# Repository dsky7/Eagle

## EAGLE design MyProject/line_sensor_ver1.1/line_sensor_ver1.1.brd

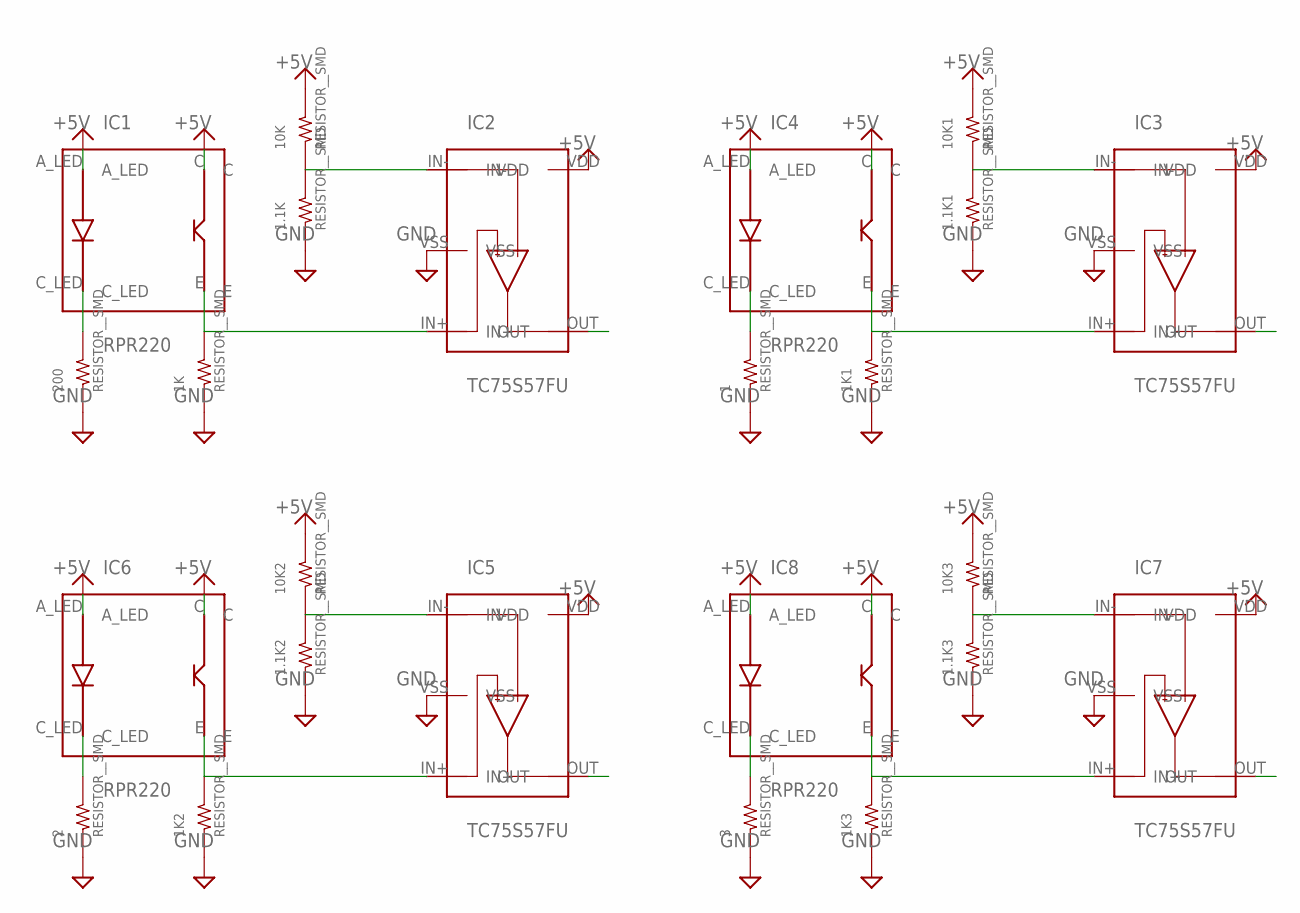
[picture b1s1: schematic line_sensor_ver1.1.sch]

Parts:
1, 1.1K, 1.1K1, 1.1K2, 1.1K3, 1K, 1K1, 1K2, 1K3, 2, 3, 10K, 10K1, 10K2, 10K3, 200: RESISTOR__SMD; 1608
IC1, IC4, IC6, IC8: RPR220
IC2, IC3, IC5, IC7: TC75S57FU; SSOP5-P-0.65A

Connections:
+5V: 10K.2, 10K1.2, 10K2.2, 10K3.2, IC1.A_LED, IC1.C, IC2.VDD, IC3.VDD, IC4.A_LED, IC4.C, IC5.VDD, IC6.A_LED, IC6.C, IC7.VDD, IC8.A_LED, IC8.C
GND: 1.1, 1.1K.1, 1.1K1.1, 1.1K2.1, 1.1K3.1, 1K.1, 1K1.1, 1K2.1, 1K3.1, 2.1, 3.1, 200.1, IC2.VSS, IC3.VSS, IC5.VSS, IC7.VSS
unnamed: 1.1K.2, 10K.1, IC2.IN-
unnamed: 1K.2, IC1.E, IC2.IN+
unnamed: 200.2, IC1.C_LED
unnamed: 1.1K1.2, 10K1.1, IC3.IN-
unnamed: 1K1.2, IC3.IN+, IC4.E
unnamed: 1.2, IC4.C_LED
unnamed: 1.1K3.2, 10K3.1, IC7.IN-
unnamed: 1.1K2.2, 10K2.1, IC5.IN-
unnamed: 1K3.2, IC7.IN+, IC8.E
unnamed: 1K2.2, IC5.IN+, IC6.E
unnamed: 2.2, IC6.C_LED
unnamed: 3.2, IC8.C_LED
OUT1: IC2.OUT
OUT2: IC3.OUT
OUT3: IC5.OUT
OUT4: IC7.OUT

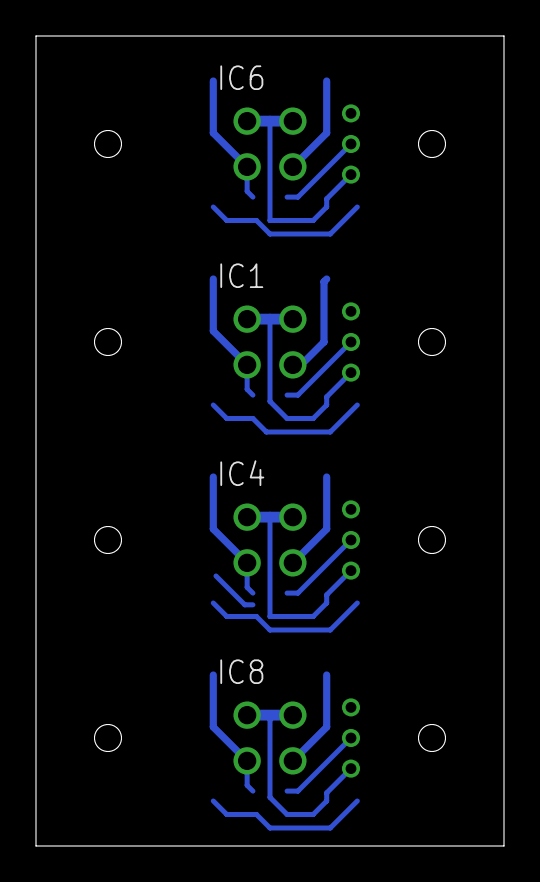
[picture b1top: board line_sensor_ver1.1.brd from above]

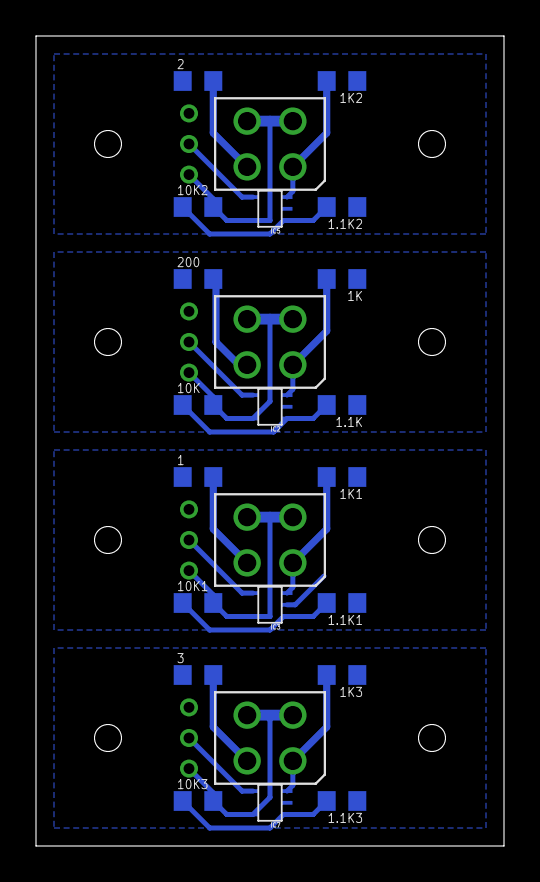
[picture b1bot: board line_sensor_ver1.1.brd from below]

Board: 2 copper layers, 26.0 x 45.0 mm, 24 parts (20 on the bottom side), 14 nets.

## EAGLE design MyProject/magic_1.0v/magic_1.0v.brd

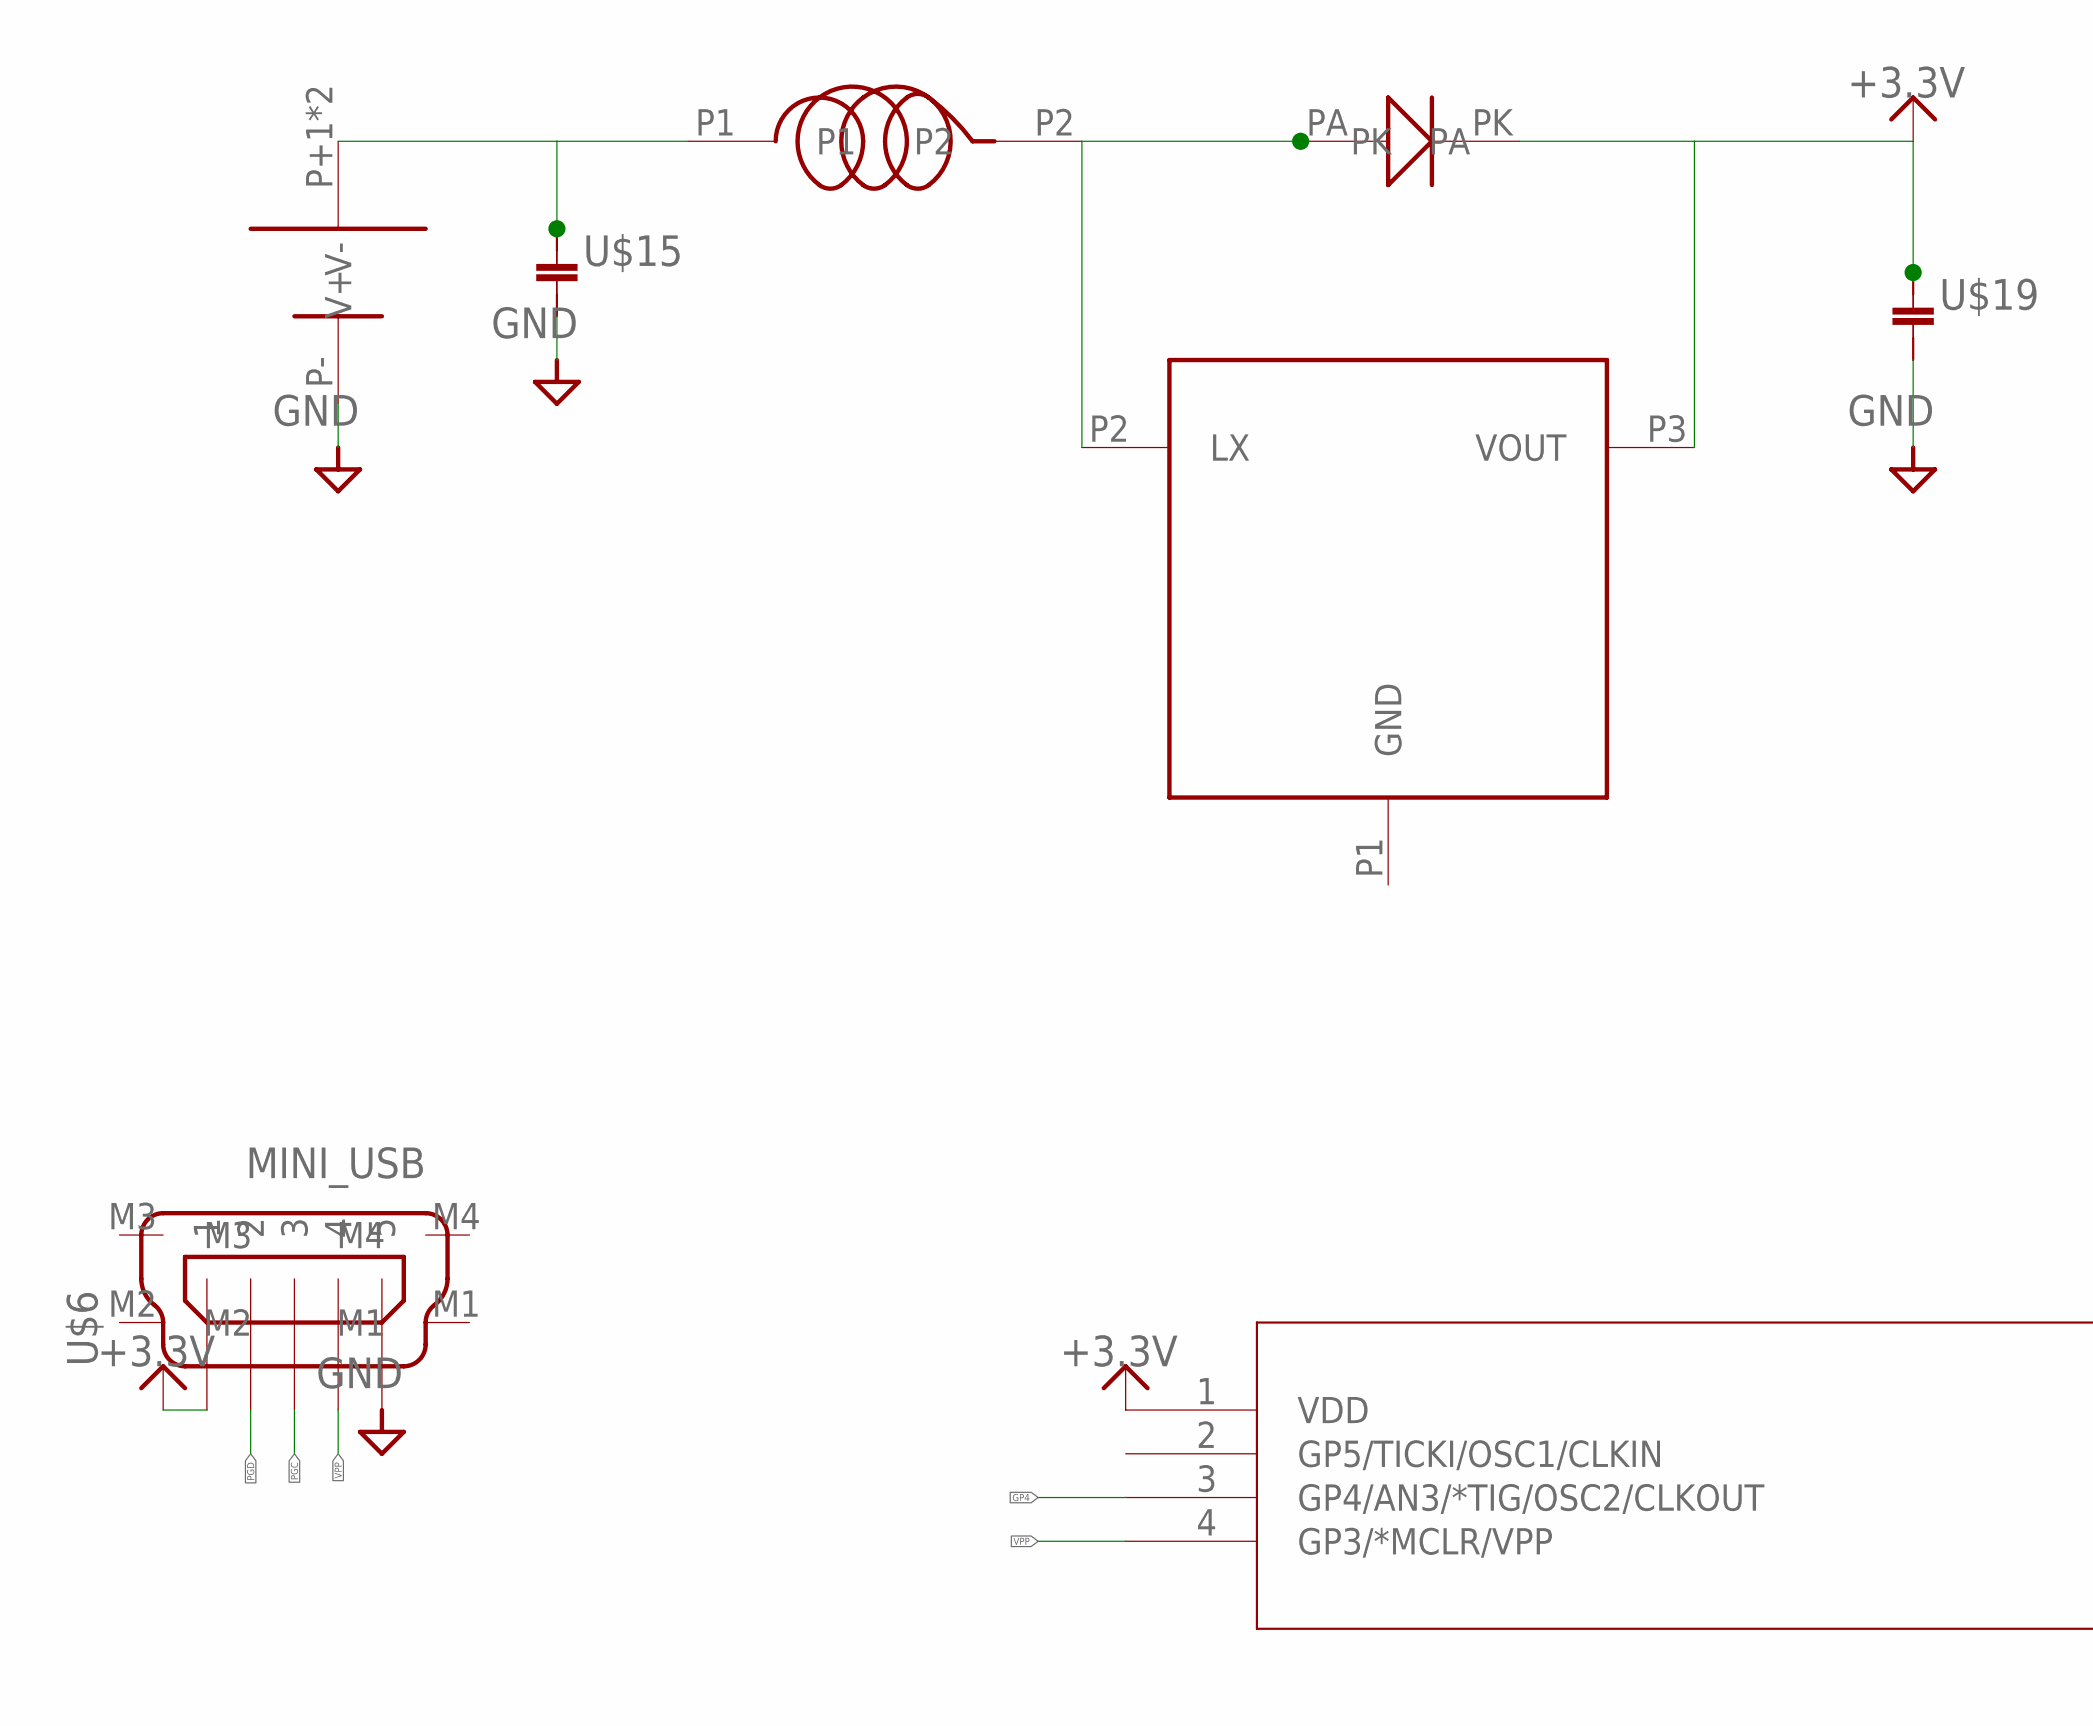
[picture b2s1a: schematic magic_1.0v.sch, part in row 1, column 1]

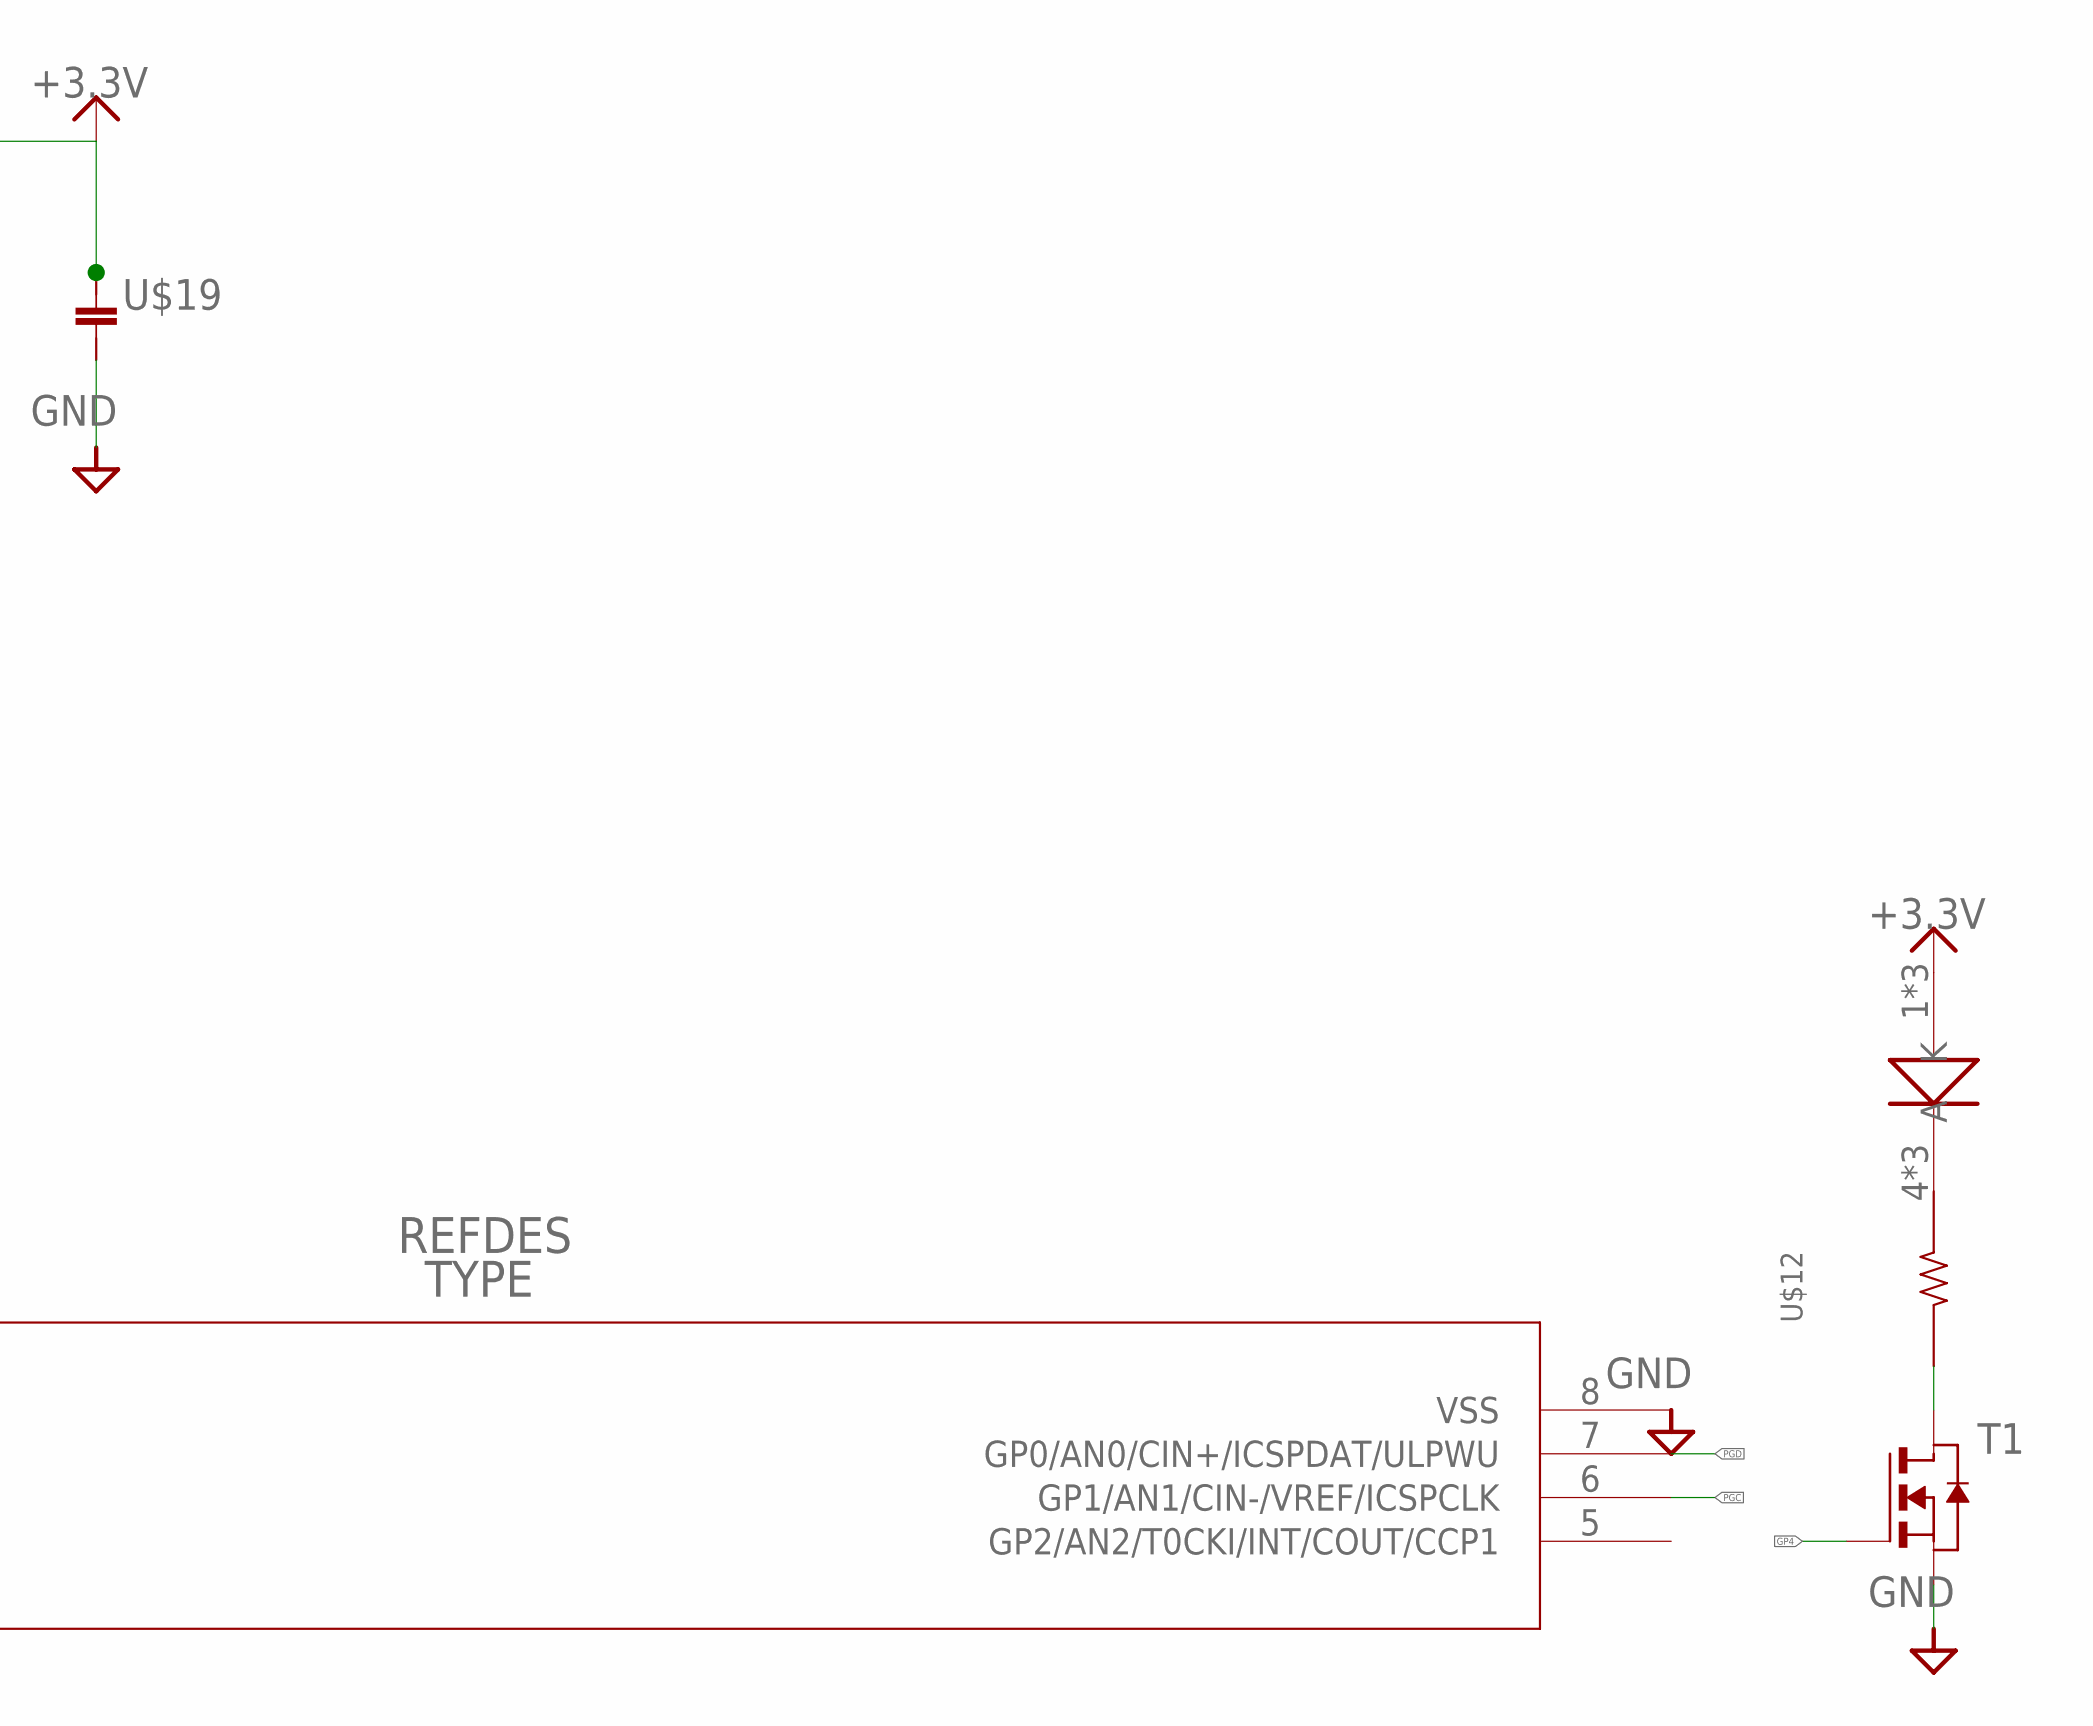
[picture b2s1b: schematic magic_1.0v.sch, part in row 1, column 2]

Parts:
T1: NMOSSOT23; SOT-23
U$1: PIC12F683-X/SN; SOIC8-N_MC
U$2: CR2032; SMTM2032
U$6: MINI_USB
U$9: OSB64; ＯＳＢ６４
U$12: RESISTOR__SMD; 1608
U$13: NPI16W
U$14: HT7733; SOT23
U$15: 3225
U$17: RSX101; TUMD2
U$19: 2012

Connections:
+3.3V: U$1.1 (VDD), U$6.1, U$9.1 (A), U$9.2 (A), U$9.3 (A), U$14.P3 (VOUT), U$17.PK, U$19.1
GND: T1.2 (S), U$1.8 (VSS), U$2.P- (V-), U$6.5, U$15.P$2 (2), U$19.2
GP4: T1.3 (G), U$1.3 (GP4/AN3/*TIG/OSC2/CLKOUT)
unnamed: U$9.4 (K), U$9.5 (K), U$9.6 (K), U$12.2
unnamed: T1.1 (D), U$12.1
unnamed: U$2.P+1 (V+), U$2.P+2 (V+), U$13.P1, U$15.P$1 (1)
unnamed: U$13.P2, U$14.P2 (LX), U$17.PA
PGC: U$1.6 (GP1/AN1/CIN-/VREF/ICSPCLK), U$6.3
PGD: U$1.7 (GP0/AN0/CIN+/ICSPDAT/ULPWU), U$6.2
VPP: U$1.4 (GP3/*MCLR/VPP), U$6.4

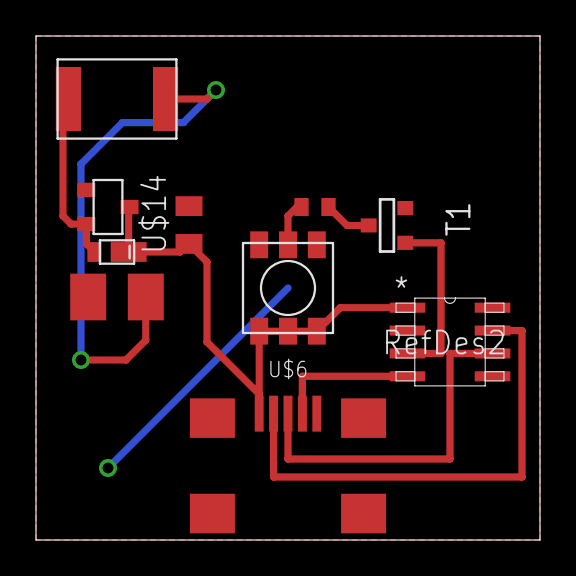
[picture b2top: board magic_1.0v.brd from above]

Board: 2 copper layers, 28.0 x 28.0 mm, 11 parts (1 on the bottom side), 10 nets.

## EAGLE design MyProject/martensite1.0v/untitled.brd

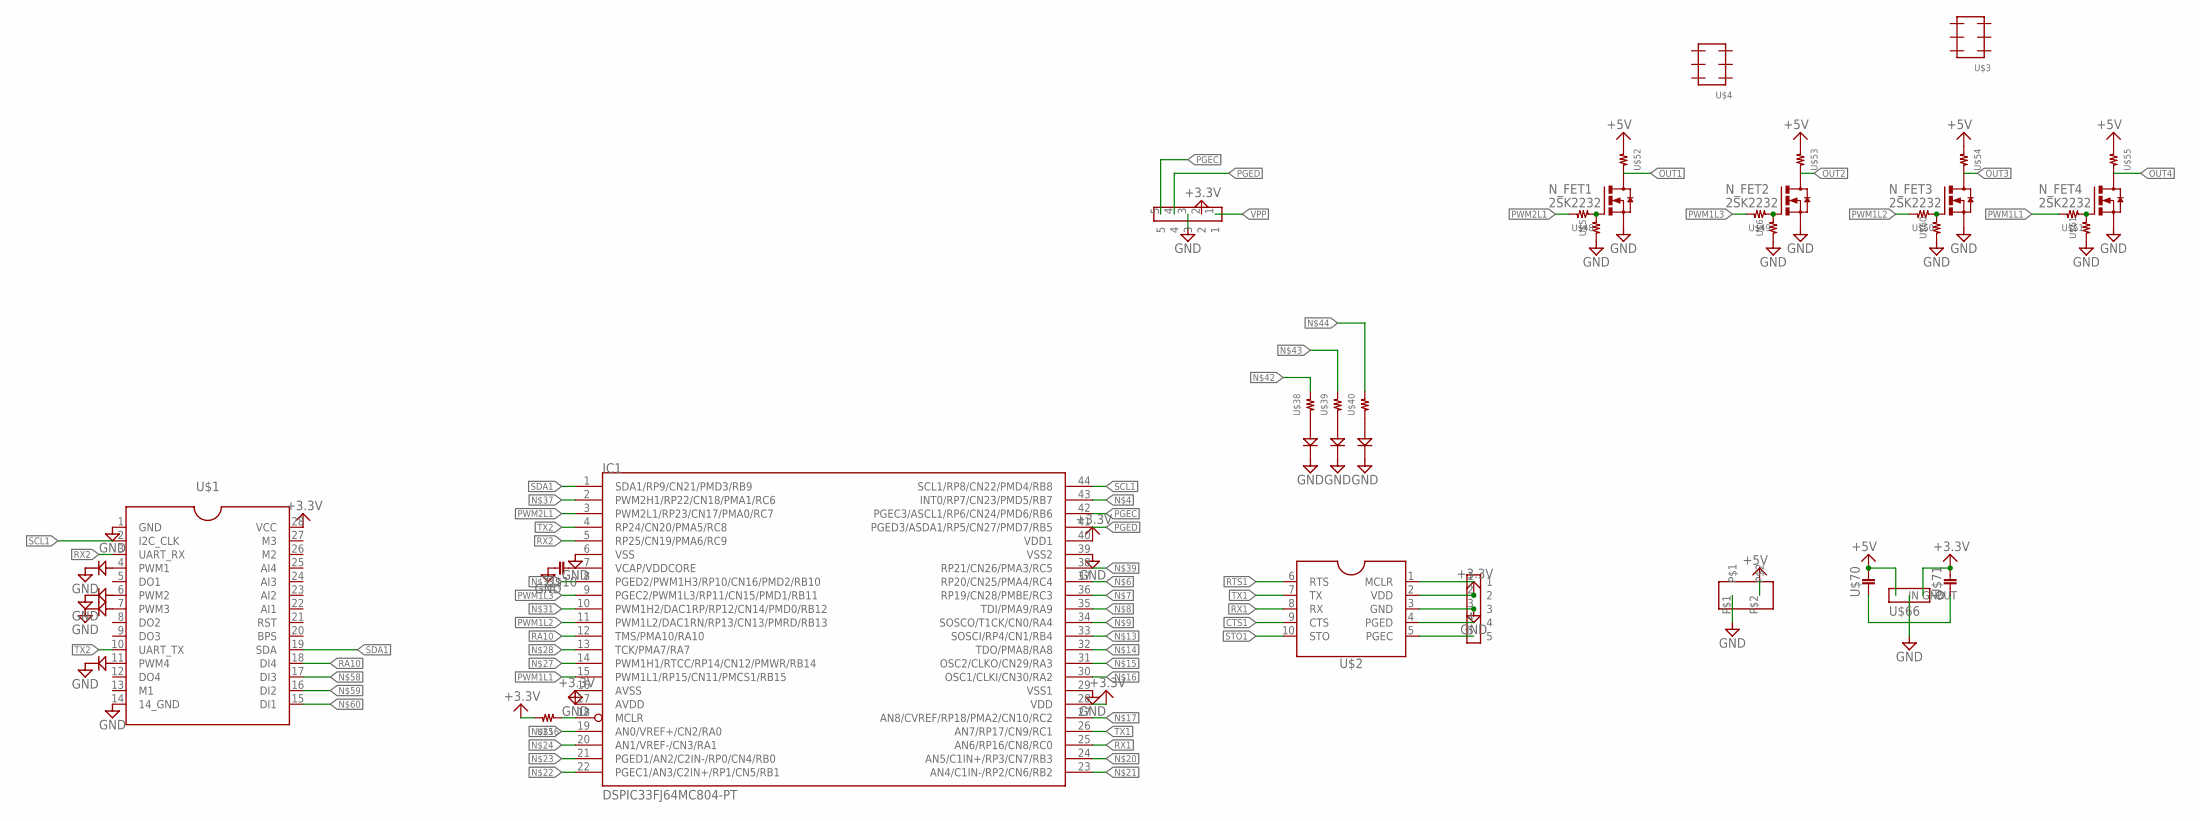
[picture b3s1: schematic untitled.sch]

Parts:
IC1: DSPIC33FJ64MC804-PT; TQFP44
N_FET1, N_FET2, N_FET3, N_FET4: 2SK2232; TO-220_V
U$1: TWE-LITE; DIP28
U$2: SBDBT; DIL10
U$3, U$4: PIN_HEADER_32; PIN_HEADER_3*2
U$5, U$6, U$16, U$38, U$39, U$40, U$48, U$49, U$50, U$51, U$52, U$53, U$54, U$55, U$60, U$61: RESISTOR__SMD; 1608
U$10: 2012
U$18, U$24: PIN_HEADER_5
U$27, U$28, U$29, U$30: 5MMLED; 5MM
U$35, U$36, U$37: 3MMLED; 3MM
U$66: TA48M033F; ＴＡ４８
U$70: 1608
U$71: 3225
U$72: PIN_HEADER_2; PIN_HEADER_2S

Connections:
+3.3V: IC1.17 (AVDD), IC1.28 (VDD), IC1.40 (VDD1), U$1.28 (VCC), U$2.2 (VDD), U$16.2, U$18.2, U$24.2, U$66.3 (OUT), U$71.P$1 (1)
+5V: U$52.1, U$53.1, U$54.1, U$55.1, U$66.1 (IN), U$70.P$1 (1), U$72.P$2
CTS1: U$2.9 (CTS)
GND: IC1.6 (VSS), IC1.16 (AVSS), IC1.29 (VSS1), IC1.39 (VSS2), N_FET1.3 (S), N_FET2.3 (S), N_FET3.3 (S), N_FET4.3 (S), U$1.1 (GND), U$1.14 (14_GND), U$2.3 (GND), U$5.1, U$6.1, U$10.1, U$18.3, U$24.3, U$27.K, U$28.K, U$29.K, U$30.K, U$35.K, U$36.K, U$37.K, U$60.1, U$61.1, U$66.2 (GND), U$70.P$2 (2), U$71.P$2 (2), U$72.P$1
unnamed: U$35.A, U$38.1
unnamed: U$2.4 (PGED), U$24.4
unnamed: U$2.1 (MCLR), U$24.1
unnamed: U$2.5 (PGEC), U$24.5
unnamed: U$1.4 (PWM1), U$27.A
unnamed: U$1.6 (PWM2), U$28.A
unnamed: U$1.7 (PWM3), U$29.A
unnamed: U$1.11 (PWM4), U$30.A
unnamed: U$36.A, U$39.1
unnamed: U$37.A, U$40.1
unnamed: N_FET1.1 (G), U$5.2, U$48.1
unnamed: N_FET2.1 (G), U$6.2, U$49.1
unnamed: N_FET3.1 (G), U$50.1, U$60.2
unnamed: N_FET4.1 (G), U$51.1, U$61.2
OUT1: N_FET1.2 (D), U$52.2
OUT2: N_FET2.2 (D), U$53.2
OUT3: N_FET3.2 (D), U$54.2
OUT4: N_FET4.2 (D), U$55.2
PGEC: IC1.42 (PGEC3/ASCL1/RP6/CN24/PMD6/RB6), U$18.5
PGED: IC1.41 (PGED3/ASDA1/RP5/CN27/PMD7/RB5), U$18.4
PWM1L1: IC1.15 (PWM1L1/RP15/CN11/PMCS1/RB15), U$51.2
PWM1L2: IC1.11 (PWM1L2/DAC1RN/RP13/CN13/PMRD/RB13), U$50.2
PWM1L3: IC1.9 (PGEC2/PWM1L3/RP11/CN15/PMD1/RB11), U$49.2
PWM2L1: IC1.3 (PWM2L1/RP23/CN17/PMA0/RC7), U$48.2
RA10: IC1.12 (TMS/PMA10/RA10), U$1.18 (DI4)
RTS1: U$2.6 (RTS)
RX1: IC1.25 (AN6/RP16/CN8/RC0), U$2.8 (RX)
RX2: IC1.5 (RP25/CN19/PMA6/RC9), U$1.3 (UART_RX)
SCL1: IC1.44 (SCL1/RP8/CN22/PMD4/RB8), U$1.2 (I2C_CLK)
SDA1: IC1.1 (SDA1/RP9/CN21/PMD3/RB9), U$1.19 (SDA)
STO1: U$2.10 (STO)
TX1: IC1.26 (AN7/RP17/CN9/RC1), U$2.7 (TX)
TX2: IC1.4 (RP24/CN20/PMA5/RC8), U$1.10 (UART_TX)
VCAP/VDDCORE: IC1.7 (VCAP/VDDCORE), U$10.2
VPP: IC1.18 (MCLR), U$16.1, U$18.1

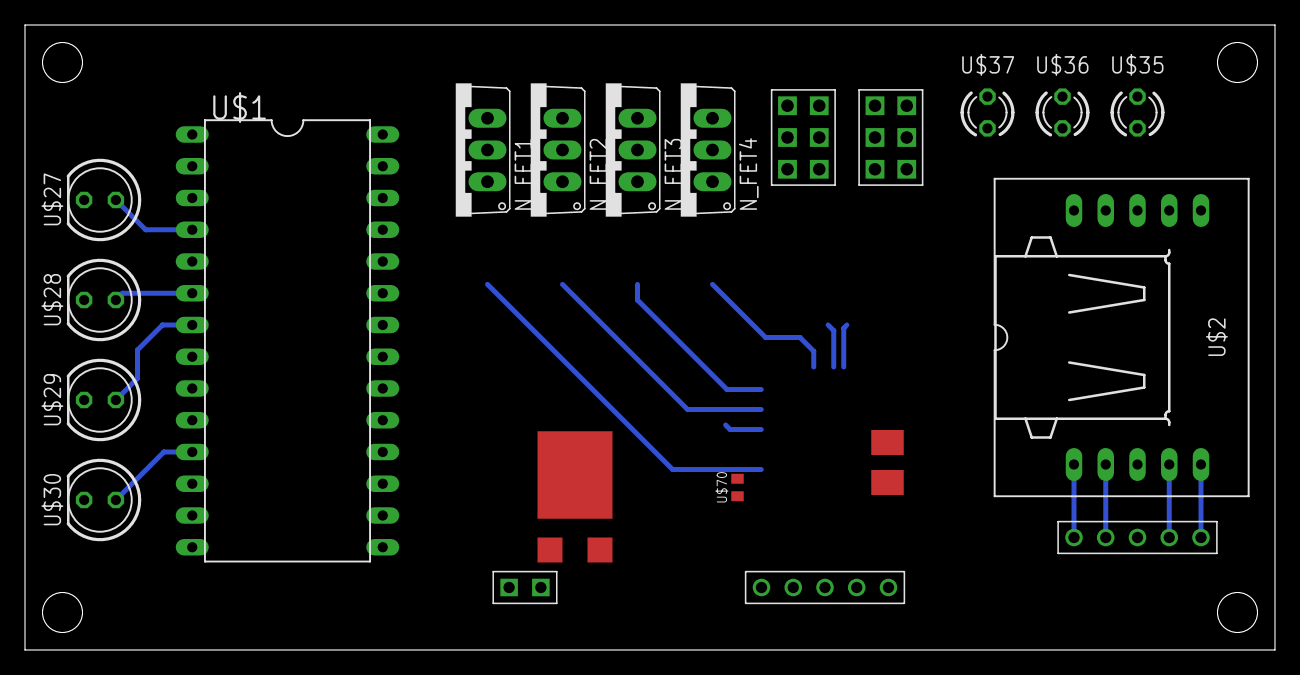
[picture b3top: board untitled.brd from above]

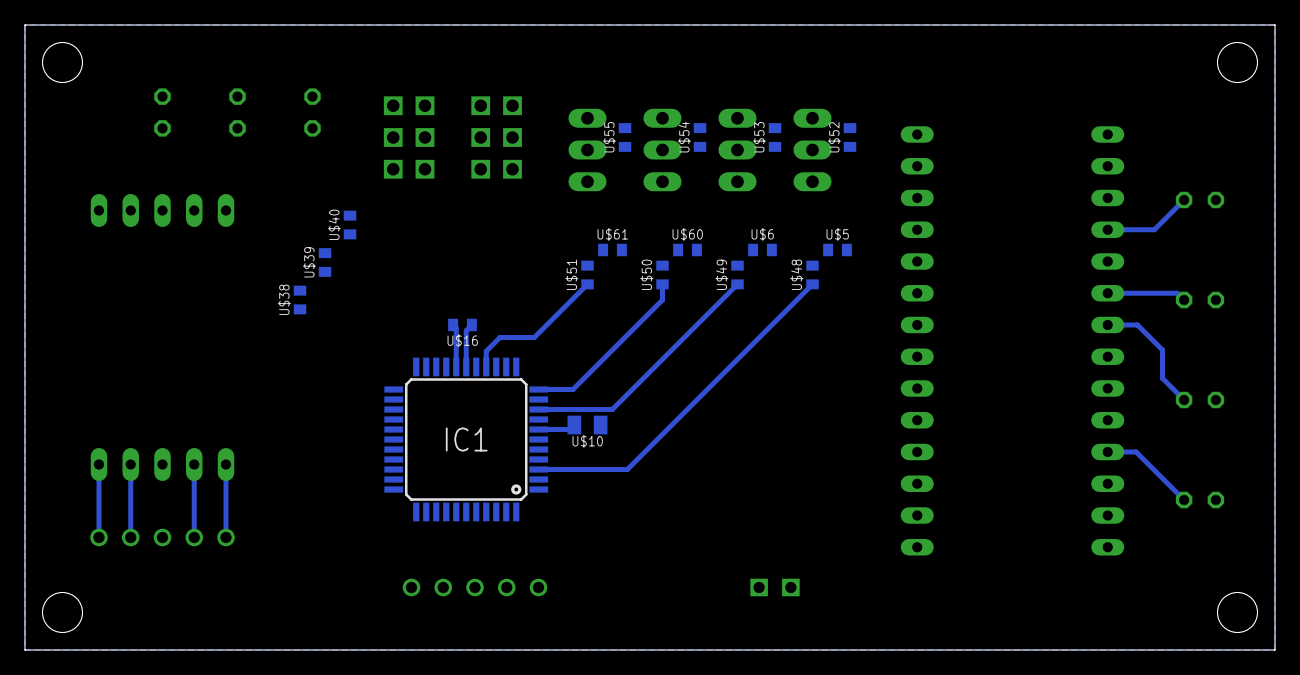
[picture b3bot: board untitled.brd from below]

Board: 2 copper layers, 100.0 x 50.0 mm, 39 parts (18 on the bottom side), 36 nets.

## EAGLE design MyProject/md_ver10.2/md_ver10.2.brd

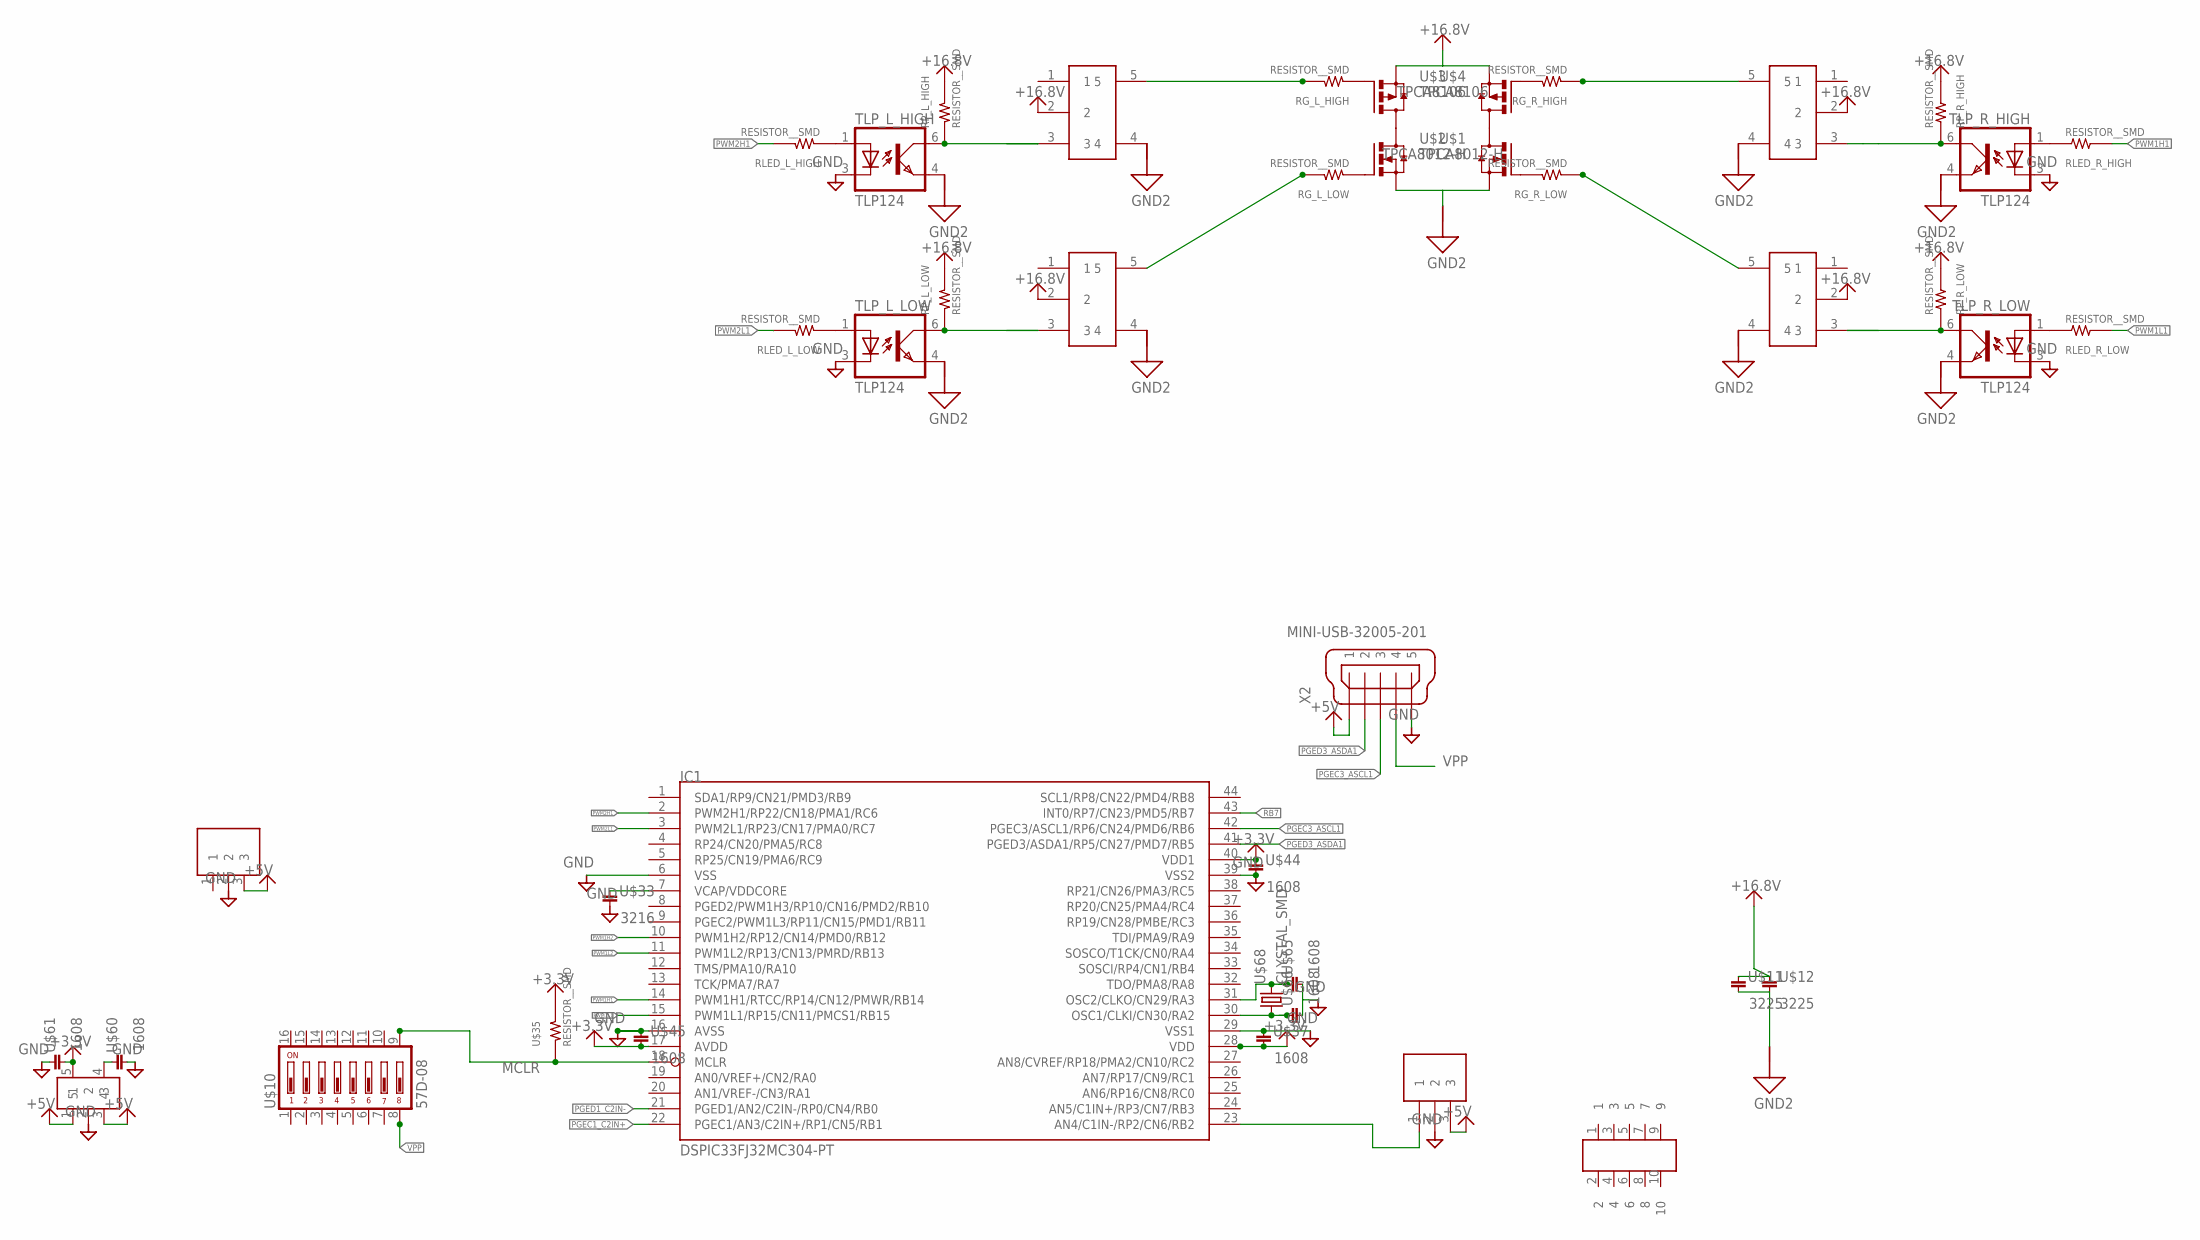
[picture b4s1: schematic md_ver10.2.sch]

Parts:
IC1: DSPIC33FJ32MC304-PT; TQFP44
IC_L_HIGH: MCP1415; SOT23-5L
IC_L_LOW: MCP1415; SOT23-5L
IC_R_HIGH: MCP1415; SOT23-5L
IC_R_LOW: MCP1415; SOT23-5L
RG_L_HIGH: RESISTOR__SMD; 1608
RG_L_LOW: RESISTOR__SMD; 1608
RG_R_HIGH: RESISTOR__SMD; 1608
RG_R_LOW: RESISTOR__SMD; 1608
RLED_L_HIGH: RESISTOR__SMD; 1608
RLED_L_LOW: RESISTOR__SMD; 1608
RLED_R_HIGH: RESISTOR__SMD; 1608
RLED_R_LOW: RESISTOR__SMD; 1608
RP_L_HIGH: RESISTOR__SMD; 1608
RP_L_LOW: RESISTOR__SMD; 1608
RP_R_HIGH: RESISTOR__SMD; 1608
RP_R_LOW: RESISTOR__SMD; 1608
TLP_L_HIGH: TLP124; 11−4C1
TLP_L_LOW: TLP124; 11−4C1
TLP_R_HIGH: TLP124; 11−4C1
TLP_R_LOW: TLP124; 11−4C1
U$1, U$2: TPCA8012-H; 2-5Q1A
U$3, U$4: TPCA8106; 2-5Q1A
U$7: ＰＬ－ＩＲＭ
U$8: Ｒ－７８Ｅ５．０
U$9: TAR5SB; SSOP5-P-0.95
U$10: 57D-08; 57D
U$11, U$12: 3225
U$15: PIN_HEADER_52; PIN_HEADER_5*2
U$33: 3216
U$35: RESISTOR__SMD; 1608
U$37, U$44, U$45, U$60, U$61, U$65, U$66: 1608
U$68: CLYSTAL_SMD; CRYSTAL_SMD
X2: MINI-USB-32005-201; 32005-201

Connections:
+3.3V: IC1.17 (AVDD), IC1.28 (VDD), IC1.40 (VDD1), U$9.5, U$35.2, U$37.P$2 (2), U$44.P$1 (1), U$45.P$2 (2), U$61.P$2 (2)
+5V: U$7.3, U$8.3, U$9.1, U$9.3, X2.1
+16.8V: IC_L_HIGH.2, IC_L_LOW.2, IC_R_HIGH.2, IC_R_LOW.2, RP_L_HIGH.2, RP_L_LOW.2, RP_R_HIGH.2, RP_R_LOW.2, U$3.1 (S), U$3.2 (S), U$3.3 (S), U$4.1 (S), U$4.2 (S), U$4.3 (S), U$11.P$1 (1), U$12.P$1 (1)
GND: IC1.6 (VSS), IC1.16 (AVSS), IC1.29 (VSS1), IC1.39 (VSS2), TLP_L_HIGH.3 (C), TLP_L_LOW.3 (C), TLP_R_HIGH.3 (C), TLP_R_LOW.3 (C), U$7.2, U$8.2, U$9.2, U$33.P$2 (2), U$37.P$1 (1), U$44.P$2 (2), U$45.P$1 (1), U$60.P$2 (2), U$61.P$1 (1), U$65.P$2 (2), U$66.P$2 (2), X2.5
GND2: IC_L_HIGH.4, IC_L_LOW.4, IC_R_HIGH.4, IC_R_LOW.4, TLP_L_HIGH.4 (EMIT), TLP_L_LOW.4 (EMIT), TLP_R_HIGH.4 (EMIT), TLP_R_LOW.4 (EMIT), U$1.1 (S), U$1.2 (S), U$1.3 (S), U$2.1 (S), U$2.2 (S), U$2.3 (S), U$11.P$2 (2), U$12.P$2 (2)
M1: U$2.5 (D), U$2.6 (D), U$2.7 (D), U$2.8 (D), U$3.5 (D), U$3.6 (D), U$3.7 (D), U$3.8 (D)
M2: U$1.5 (D), U$1.6 (D), U$1.7 (D), U$1.8 (D), U$4.5 (D), U$4.6 (D), U$4.7 (D), U$4.8 (D)
MCLR: IC1.18 (MCLR), U$10.9, U$35.1
unnamed: RG_L_LOW.1, U$2.4 (G)
unnamed: U$9.4, U$60.P$1 (1)
unnamed: RLED_L_LOW.1, TLP_L_LOW.1 (A)
unnamed: RG_R_LOW.2, U$1.4 (G)
unnamed: IC_L_LOW.5, RG_L_LOW.2
unnamed: IC_L_LOW.3, RP_L_LOW.1, TLP_L_LOW.6 (COL)
unnamed: IC_R_LOW.5, RG_R_LOW.1
unnamed: RLED_R_LOW.1, TLP_R_LOW.1 (A)
unnamed: IC_L_HIGH.3, RP_L_HIGH.1, TLP_L_HIGH.6 (COL)
unnamed: RLED_L_HIGH.1, TLP_L_HIGH.1 (A)
unnamed: IC_L_HIGH.5, RG_L_HIGH.2
unnamed: IC_R_HIGH.3, RP_R_HIGH.1, TLP_R_HIGH.6 (COL)
unnamed: RLED_R_HIGH.1, TLP_R_HIGH.1 (A)
unnamed: IC1.23 (AN4/C1IN-/RP2/CN6/RB2), U$7.1
unnamed: IC_R_HIGH.5, RG_R_HIGH.1
unnamed: RG_L_HIGH.1, U$3.4 (G)
unnamed: RG_R_HIGH.2, U$4.4 (G)
unnamed: IC1.30 (OSC1/CLKI/CN30/RA2), U$66.P$1 (1), U$68.1
unnamed: IC1.31 (OSC2/CLKO/CN29/RA3), U$65.P$1 (1), U$68.2
PGEC1_C2IN+: IC1.22 (PGEC1/AN3/C2IN+/RP1/CN5/RB1)
PGEC3_ASCL1: IC1.42 (PGEC3/ASCL1/RP6/CN24/PMD6/RB6), X2.3
PGED1_C2IN-: IC1.21 (PGED1/AN2/C2IN-/RP0/CN4/RB0)
PGED3_ASDA1: IC1.41 (PGED3/ASDA1/RP5/CN27/PMD7/RB5), X2.2
PWM1H1: IC1.14 (PWM1H1/RTCC/RP14/CN12/PMWR/RB14), RLED_R_HIGH.2
PWM1H2: IC1.10 (PWM1H2/RP12/CN14/PMD0/RB12)
PWM1L1: IC1.15 (PWM1L1/RP15/CN11/PMCS1/RB15), RLED_R_LOW.2
PWM1L2: IC1.11 (PWM1L2/RP13/CN13/PMRD/RB13)
PWM2H1: IC1.2 (PWM2H1/RP22/CN18/PMA1/RC6), RLED_L_HIGH.2
PWM2L1: IC1.3 (PWM2L1/RP23/CN17/PMA0/RC7), RLED_L_LOW.2
RB7: IC1.43 (INT0/RP7/CN23/PMD5/RB7)
TLP_R_LOW: IC_R_LOW.3, RP_R_LOW.1, TLP_R_LOW.6 (COL)
VCAP/VDDCORE: IC1.7 (VCAP/VDDCORE), U$33.P$1 (1)
VPP: U$10.8, X2.4

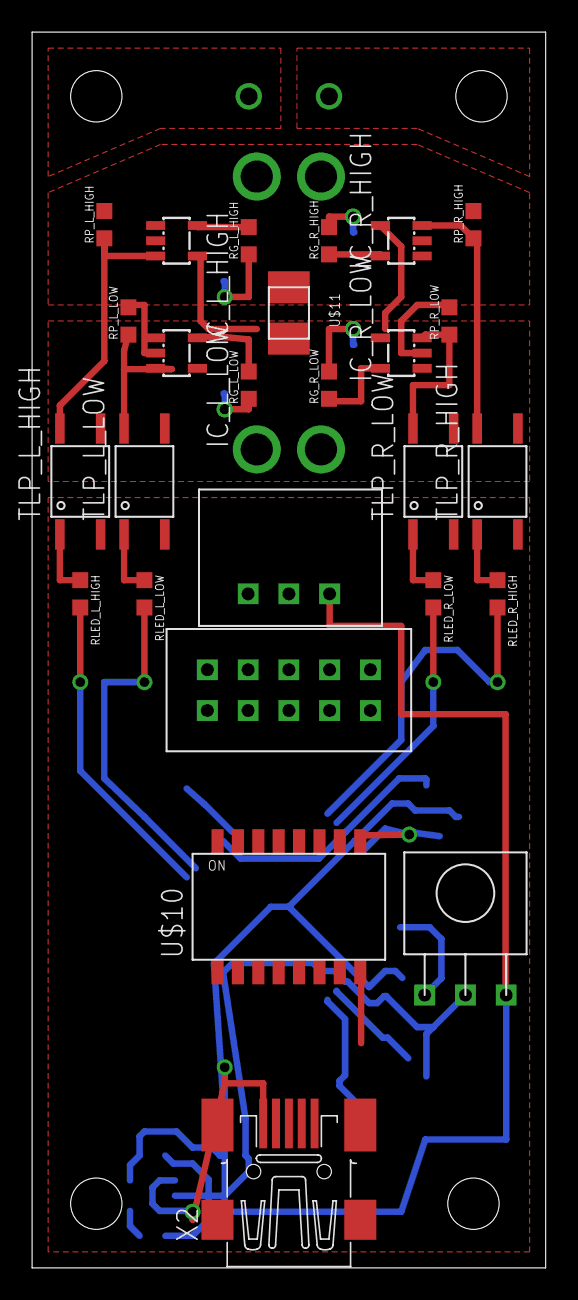
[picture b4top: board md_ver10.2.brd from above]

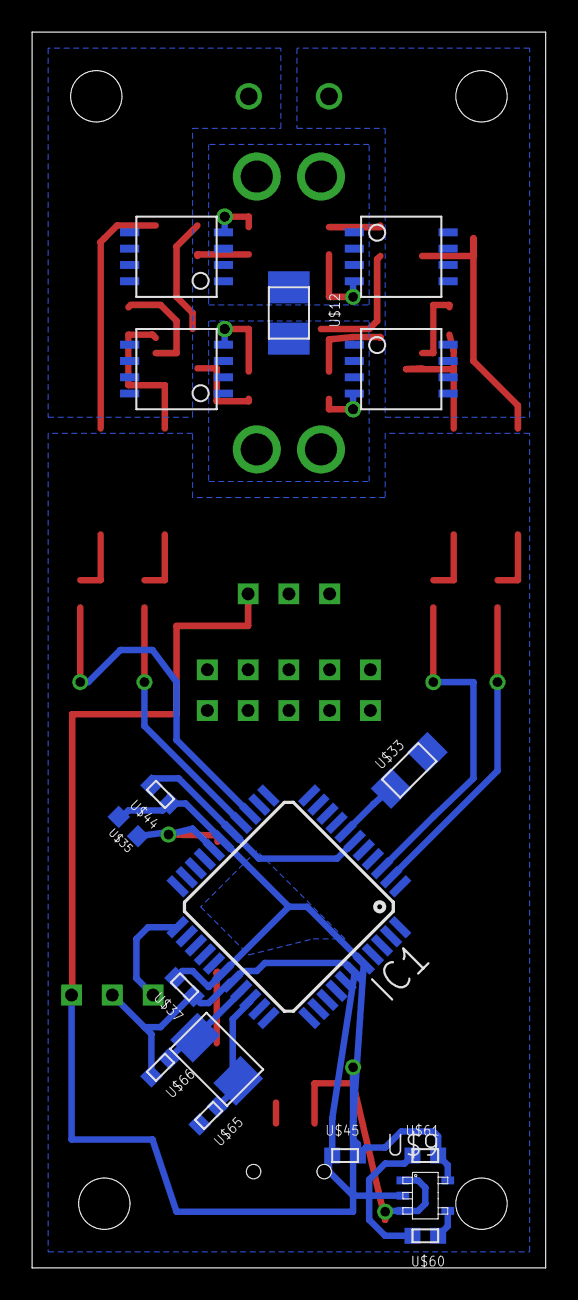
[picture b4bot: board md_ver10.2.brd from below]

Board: 2 copper layers, 32.0 x 77.0 mm, 43 parts (17 on the bottom side), 36 nets.
